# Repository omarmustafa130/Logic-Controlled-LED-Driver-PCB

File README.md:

# Logic-Controlled-LED-Driver-PCB

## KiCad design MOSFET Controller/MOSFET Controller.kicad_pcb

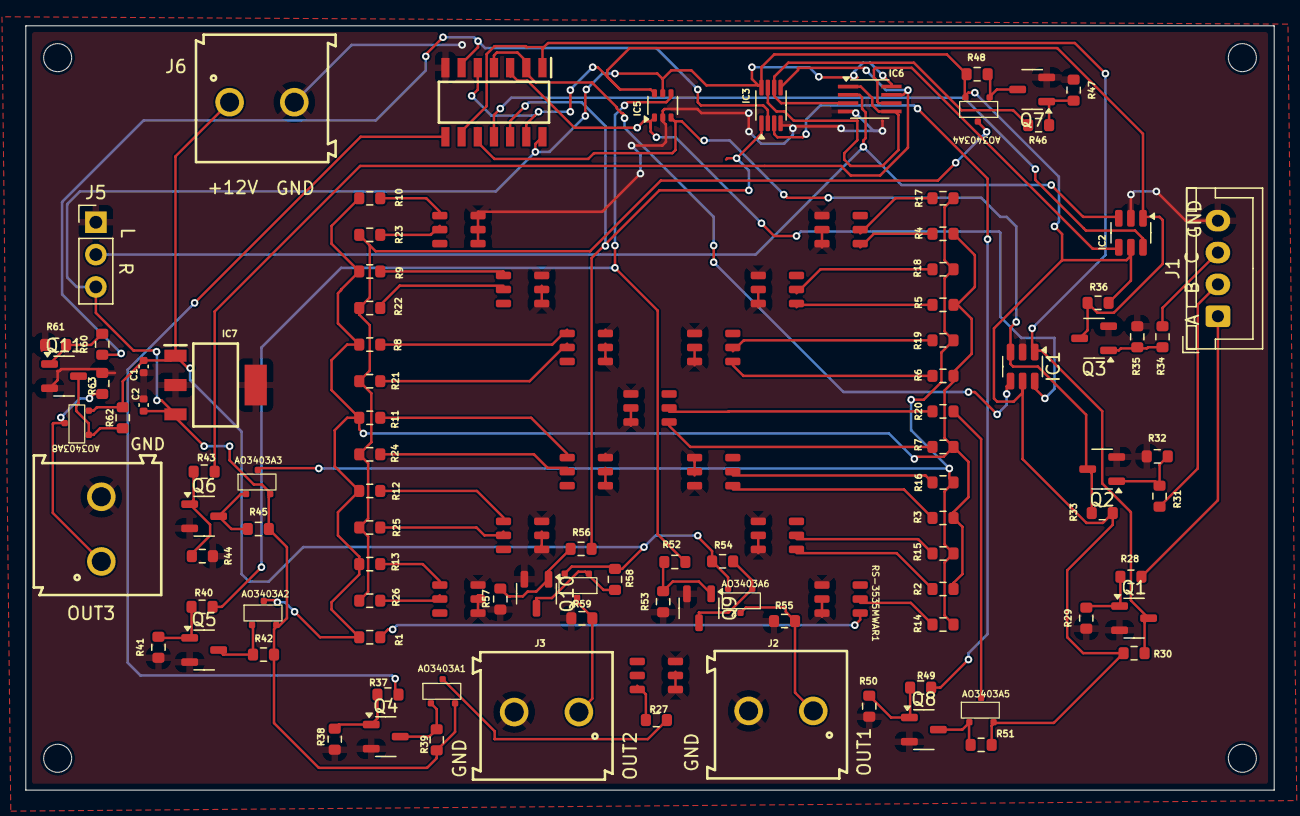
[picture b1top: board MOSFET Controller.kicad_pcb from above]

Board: 2 copper layers, 98.0 x 60.0 mm, 115 parts (0 on the bottom side), 76 nets.

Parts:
AO3403A1, AO3403A2, AO3403A3, AO3403A4, AO3403A5, AO3403A6, AO3403A7, AO3403A8: AO3403A
C1: 0.22u; C_0402_1005Metric
C2: 0.1u; C_0402_1005Metric
H1, H2, H3, H4: MountingHole; MountingHole_2.2mm_M2
IC1, IC2: SN74LVC2G04DBVR; SOT-23-6
IC3: SN74LVC2G32DCURG4; VSSOP-8_2.3x2mm_P0.5mm
IC4: 74HCT11PW,118; SOIC127P600X175-14N - IC4
IC5: NL17SZ11DBVT1G; SOT-363_SC-70-6
IC6: TC7W08FU; SSOP-8_2.95x2.8mm_P0.65mm
IC7: LM7805MPX_NOPB; SOT230P700X180-4N
J1: B4B-EH-A_LF__SN_; JST_XH_B4B-XH-A_1x04_P2.50mm_Vertical
J2, J3, J4, J6: 691216510002S
J5: Conn_01x03_Pin; PinHeader_1x03_P2.54mm_Vertical
Q1, Q2, Q3, Q4, Q5, Q6, Q7, Q8, Q9, Q10, Q11: AO3400A; SOT-23-3
R1, R2, R3, R4, R5, R6, R7, R8, R9, R10, R11, R12, R13, R55, R59, R63: 100R; R_0603_1608Metric
R14, R15, R16, R17, R18, R19, R20, R21, R22, R23, R24, R25, R26, R27: 82R; R_0603_1608Metric
R28, R31, R34, R37, R40, R43, R46, R49, R52, R56, R60: 10; R_0603_1608Metric
R29, R30, R32, R33, R35, R36, R38, R39, R41, R42, R44, R45, R47, R48, R50, R51, R53, R54, R57, R58, R61, R62: 10k; R_0603_1608Metric
RS-3535MWAR1, RS-3535MWAR2, RS-3535MWAR3, RS-3535MWAR4, RS-3535MWAR5, RS-3535MWAR6, RS-3535MWAR7, RS-3535MWAR8, RS-3535MWAR9, RS-3535MWAR10, RS-3535MWAR11, RS-3535MWAR12, RS-3535MWAR13, RS-3535MWAR14: RS-3535MWAR

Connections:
5V: AO3403A1.2 (S), AO3403A2.2 (S), AO3403A3.2 (S), AO3403A4.2 (S), AO3403A5.2 (S), C2.1, IC1.5 (VCC), IC2.5 (VCC), IC3.8 (VCC), IC4.14 (VCC), IC5.5 (VCC), IC6.8 (VCC), IC7.3 (OUTPUT), J5.3, R30.2, R33.2, R36.2, R39.2, R42.2, R45.2, R48.2, R51.2
12V: AO3403A6.2 (S), AO3403A7.2 (S), AO3403A8.2 (S), C1.1, IC7.1 (INPUT), J6.1, R54.2, R58.2, R62.2
A: IC1.6 (1Y), IC4.3 (2A), IC5.1 (A)
A_IN: J1.1, R28.1
A_NOT: IC1.1 (1A), IC4.1 (1A), IC4.9 (3A), Q1.3, R30.1
B: IC1.4 (2Y), IC4.2 (1B), IC4.4 (2B)
BLUE_IN: IC4.8 (3Y), R37.1
BLUE_O: AO3403A1.3 (D), R27.1
B_IN: J1.2, R31.1
B_NOT: IC1.3 (2A), IC4.10 (3B), IC5.3 (B), Q2.3, R33.1
C: IC2.6 (1Y), IC4.11 (3C)
C_IN: J1.3, R34.1
C_NOT: IC2.1 (1A), IC4.5 (2C), IC4.13 (1C), IC5.6 (C), Q3.3, R36.1
GND: C1.2, C2.2, IC1.2 (GND), IC2.2 (GND), IC3.4 (GND), IC4.7 (GND), IC5.2 (GND), IC6.4 (GND), IC7.2 (GND_1), IC7.4 (GND_2), J1.4, J2.2, J3.2, J4.2, J5.1, J6.2, Q1.2, Q2.2, Q3.2, Q4.2, Q5.2, Q6.2, Q7.2, Q8.2, Q9.2, Q10.2, Q11.2, R29.1, R32.1, R35.1, R38.1, R41.1, R44.1, R47.1, R50.1, R53.1, R55.1, R57.1, R59.1, R61.1, R63.1, RS-3535MWAR1.1 (C), RS-3535MWAR1.2 (C), RS-3535MWAR1.3 (C), RS-3535MWAR2.1 (C), RS-3535MWAR2.2 (C), RS-3535MWAR2.3 (C), RS-3535MWAR3.1 (C), RS-3535MWAR3.2 (C), RS-3535MWAR3.3 (C), RS-3535MWAR4.1 (C), RS-3535MWAR4.2 (C), RS-3535MWAR4.3 (C), RS-3535MWAR5.1 (C), RS-3535MWAR5.2 (C), RS-3535MWAR5.3 (C), RS-3535MWAR6.1 (C), RS-3535MWAR6.2 (C), RS-3535MWAR6.3 (C), RS-3535MWAR7.1 (C), RS-3535MWAR7.2 (C), RS-3535MWAR7.3 (C), RS-3535MWAR8.1 (C), RS-3535MWAR8.2 (C), RS-3535MWAR8.3 (C), RS-3535MWAR9.1 (C), RS-3535MWAR9.2 (C), RS-3535MWAR9.3 (C), RS-3535MWAR10.1 (C), RS-3535MWAR10.2 (C), RS-3535MWAR10.3 (C), RS-3535MWAR11.1 (C), RS-3535MWAR11.2 (C), RS-3535MWAR11.3 (C), RS-3535MWAR12.1 (C), RS-3535MWAR12.2 (C), RS-3535MWAR12.3 (C), RS-3535MWAR13.1 (C), RS-3535MWAR13.2 (C), RS-3535MWAR13.3 (C), RS-3535MWAR14.1 (C), RS-3535MWAR14.2 (C), RS-3535MWAR14.3 (C)
GREEN1: IC3.1 (1A), IC4.12 (1Y), R56.1
GREEN1_IN: IC3.5 (2A), IC6.7 (1Y), R43.1
GREEN1_O: AO3403A3.3 (D), R14.1, R15.1, R16.1, R17.1, R18.1, R19.1
GREEN2: IC3.2 (1B), IC4.6 (2Y), R60.1
GREEN2_IN: IC3.6 (2B), IC6.3 (2Y), R46.1
GREEN2_O: AO3403A4.3 (D), R21.1, R22.1, R23.1, R24.1, R25.1, R26.1
GREEN3_IN: IC3.3 (2Y), R49.1
GREEN3_O: AO3403A5.3 (D), R20.1
GREEN_IN: IC3.7 (1Y), IC6.1 (1A), IC6.5 (2A)
JS: IC2.3 (2A), IC6.2 (1B), J5.2
JS_NOT: IC2.4 (2Y), IC6.6 (2B)
unnamed: AO3403A1.1 (G), Q4.3, R39.1
unnamed: AO3403A2.1 (G), Q5.3, R42.1
unnamed: AO3403A3.1 (G), Q6.3, R45.1
unnamed: AO3403A4.1 (G), Q7.3, R48.1
unnamed: AO3403A5.1 (G), Q8.3, R51.1
unnamed: AO3403A6.1 (G), Q9.3, R54.1
unnamed: AO3403A7.1 (G), Q10.3, R58.1
unnamed: AO3403A8.1 (G), Q11.3, R62.1
unnamed: Q1.1, R28.2, R29.2
unnamed: Q2.1, R31.2, R32.2
unnamed: Q3.1, R34.2, R35.2
unnamed: Q4.1, R37.2, R38.2
unnamed: Q5.1, R40.2, R41.2
unnamed: Q6.1, R43.2, R44.2
unnamed: Q7.1, R46.2, R47.2
unnamed: Q8.1, R49.2, R50.2
unnamed: Q9.1, R52.2, R53.2
unnamed: Q10.1, R56.2, R57.2
unnamed: Q11.1, R60.2, R61.2
unnamed: R14.2, RS-3535MWAR1.5 (G+)
unnamed: R1.2, RS-3535MWAR1.4 (R+)
unnamed: R15.2, RS-3535MWAR2.5 (G+)
unnamed: R2.2, RS-3535MWAR2.4 (R+)
unnamed: R16.2, RS-3535MWAR3.5 (G+)
unnamed: R3.2, RS-3535MWAR3.4 (R+)
unnamed: R17.2, RS-3535MWAR4.5 (G+)
unnamed: R4.2, RS-3535MWAR4.4 (R+)
unnamed: R18.2, RS-3535MWAR5.5 (G+)
unnamed: R5.2, RS-3535MWAR5.4 (R+)
unnamed: R19.2, RS-3535MWAR6.5 (G+)
unnamed: R6.2, RS-3535MWAR6.4 (R+)
unnamed: R21.2, RS-3535MWAR7.5 (G+)
unnamed: R8.2, RS-3535MWAR7.4 (R+)
unnamed: R22.2, RS-3535MWAR8.5 (G+)
unnamed: R9.2, RS-3535MWAR8.4 (R+)
unnamed: R23.2, RS-3535MWAR9.5 (G+)
unnamed: R10.2, RS-3535MWAR9.4 (R+)
unnamed: R24.2, RS-3535MWAR10.5 (G+)
unnamed: R11.2, RS-3535MWAR10.4 (R+)
unnamed: R25.2, RS-3535MWAR11.5 (G+)
unnamed: R12.2, RS-3535MWAR11.4 (R+)
unnamed: R26.2, RS-3535MWAR12.5 (G+)
unnamed: R13.2, RS-3535MWAR12.4 (R+)
unnamed: R20.2, RS-3535MWAR13.5 (G+)
unnamed: R7.2, RS-3535MWAR13.4 (R+)
unnamed: R27.2, RS-3535MWAR14.6 (B+)
OUT1: AO3403A6.3 (D), J2.1, R55.2
OUT2: AO3403A7.3 (D), J3.1, R59.2
OUT3: AO3403A8.3 (D), J4.1, R63.2
RED_IN: IC5.4 (Y), R40.1, R52.1
RED_O: AO3403A2.3 (D), R1.1, R2.1, R3.1, R4.1, R5.1, R6.1, R7.1, R8.1, R9.1, R10.1, R11.1, R12.1, R13.1

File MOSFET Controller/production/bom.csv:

Designator,Footprint,Quantity,Value,LCSC Part #
"AO3403A1, AO3403A2, AO3403A3, AO3403A4, AO3403A5, AO3403A6, AO3403A7, AO3403A8",AO3403A,8,~,
C1,0402,1,0.22u,
C2,0402,1,0.1u,
"IC1, IC2",SOT-23-6,2,SN74LVC2G04DBVR,
IC3,VSSOP-8_2.3x2mm_P0.5mm,1,SN74LVC2G32DCURG4,
IC4,SOIC127P600X175-14N - IC4,1,"74HCT11PW,118",
IC5,SOT-363_SC-70-6,1,NL17SZ11DBVT1G,
IC6,SSOP-8_2.95x2.8mm_P0.65mm,1,TC7W08FU,
IC7,SOT230P700X180-4N,1,LM7805MPX_NOPB,
J1,JST_XH_B4B-XH-A_1x04_P2.50mm_Vertical,1,B4B-EH-A_LF__SN_,
"J2, J3, J4, J6",691216510002S,4,691216510002S,
J5,PinHeader_1x03_P2.54mm_Vertical,1,Conn_01x03_Pin,
"Q1, Q10, Q11, Q2, Q3, Q4, Q5, Q6, Q7, Q8, Q9",SOT-23-3,11,AO3400A,
"R1, R10, R11, R12, R13, R2, R3, R4, R5, R55, R59, R6, R63, R7, R8, R9",0603,16,100R,
"R14, R15, R16, R17, R18, R19, R20, R21, R22, R23, R24, R25, R26, R27",0603,14,82R,
"R28, R31, R34, R37, R40, R43, R46, R49, R52, R56, R60",0603,11,10,
"R29, R30, R32, R33, R35, R36, R38, R39, R41, R42, R44, R45, R47, R48, R50, R51, R53, R54, R57, R58, R61, R62",0603,22,10k,
"RS-3535MWAR1, RS-3535MWAR10, RS-3535MWAR11, RS-3535MWAR12, RS-3535MWAR13, RS-3535MWAR14, RS-3535MWAR2, RS-3535MWAR3, RS-3535MWAR4, RS-3535MWAR5, RS-3535MWAR6, RS-3535MWAR7, RS-3535MWAR8, RS-3535MWAR9",RS-3535MWAR,14,~,

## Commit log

2025-03-16 Project finished
